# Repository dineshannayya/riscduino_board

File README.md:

# riscduino_board
Riscduino PCB Board documentation

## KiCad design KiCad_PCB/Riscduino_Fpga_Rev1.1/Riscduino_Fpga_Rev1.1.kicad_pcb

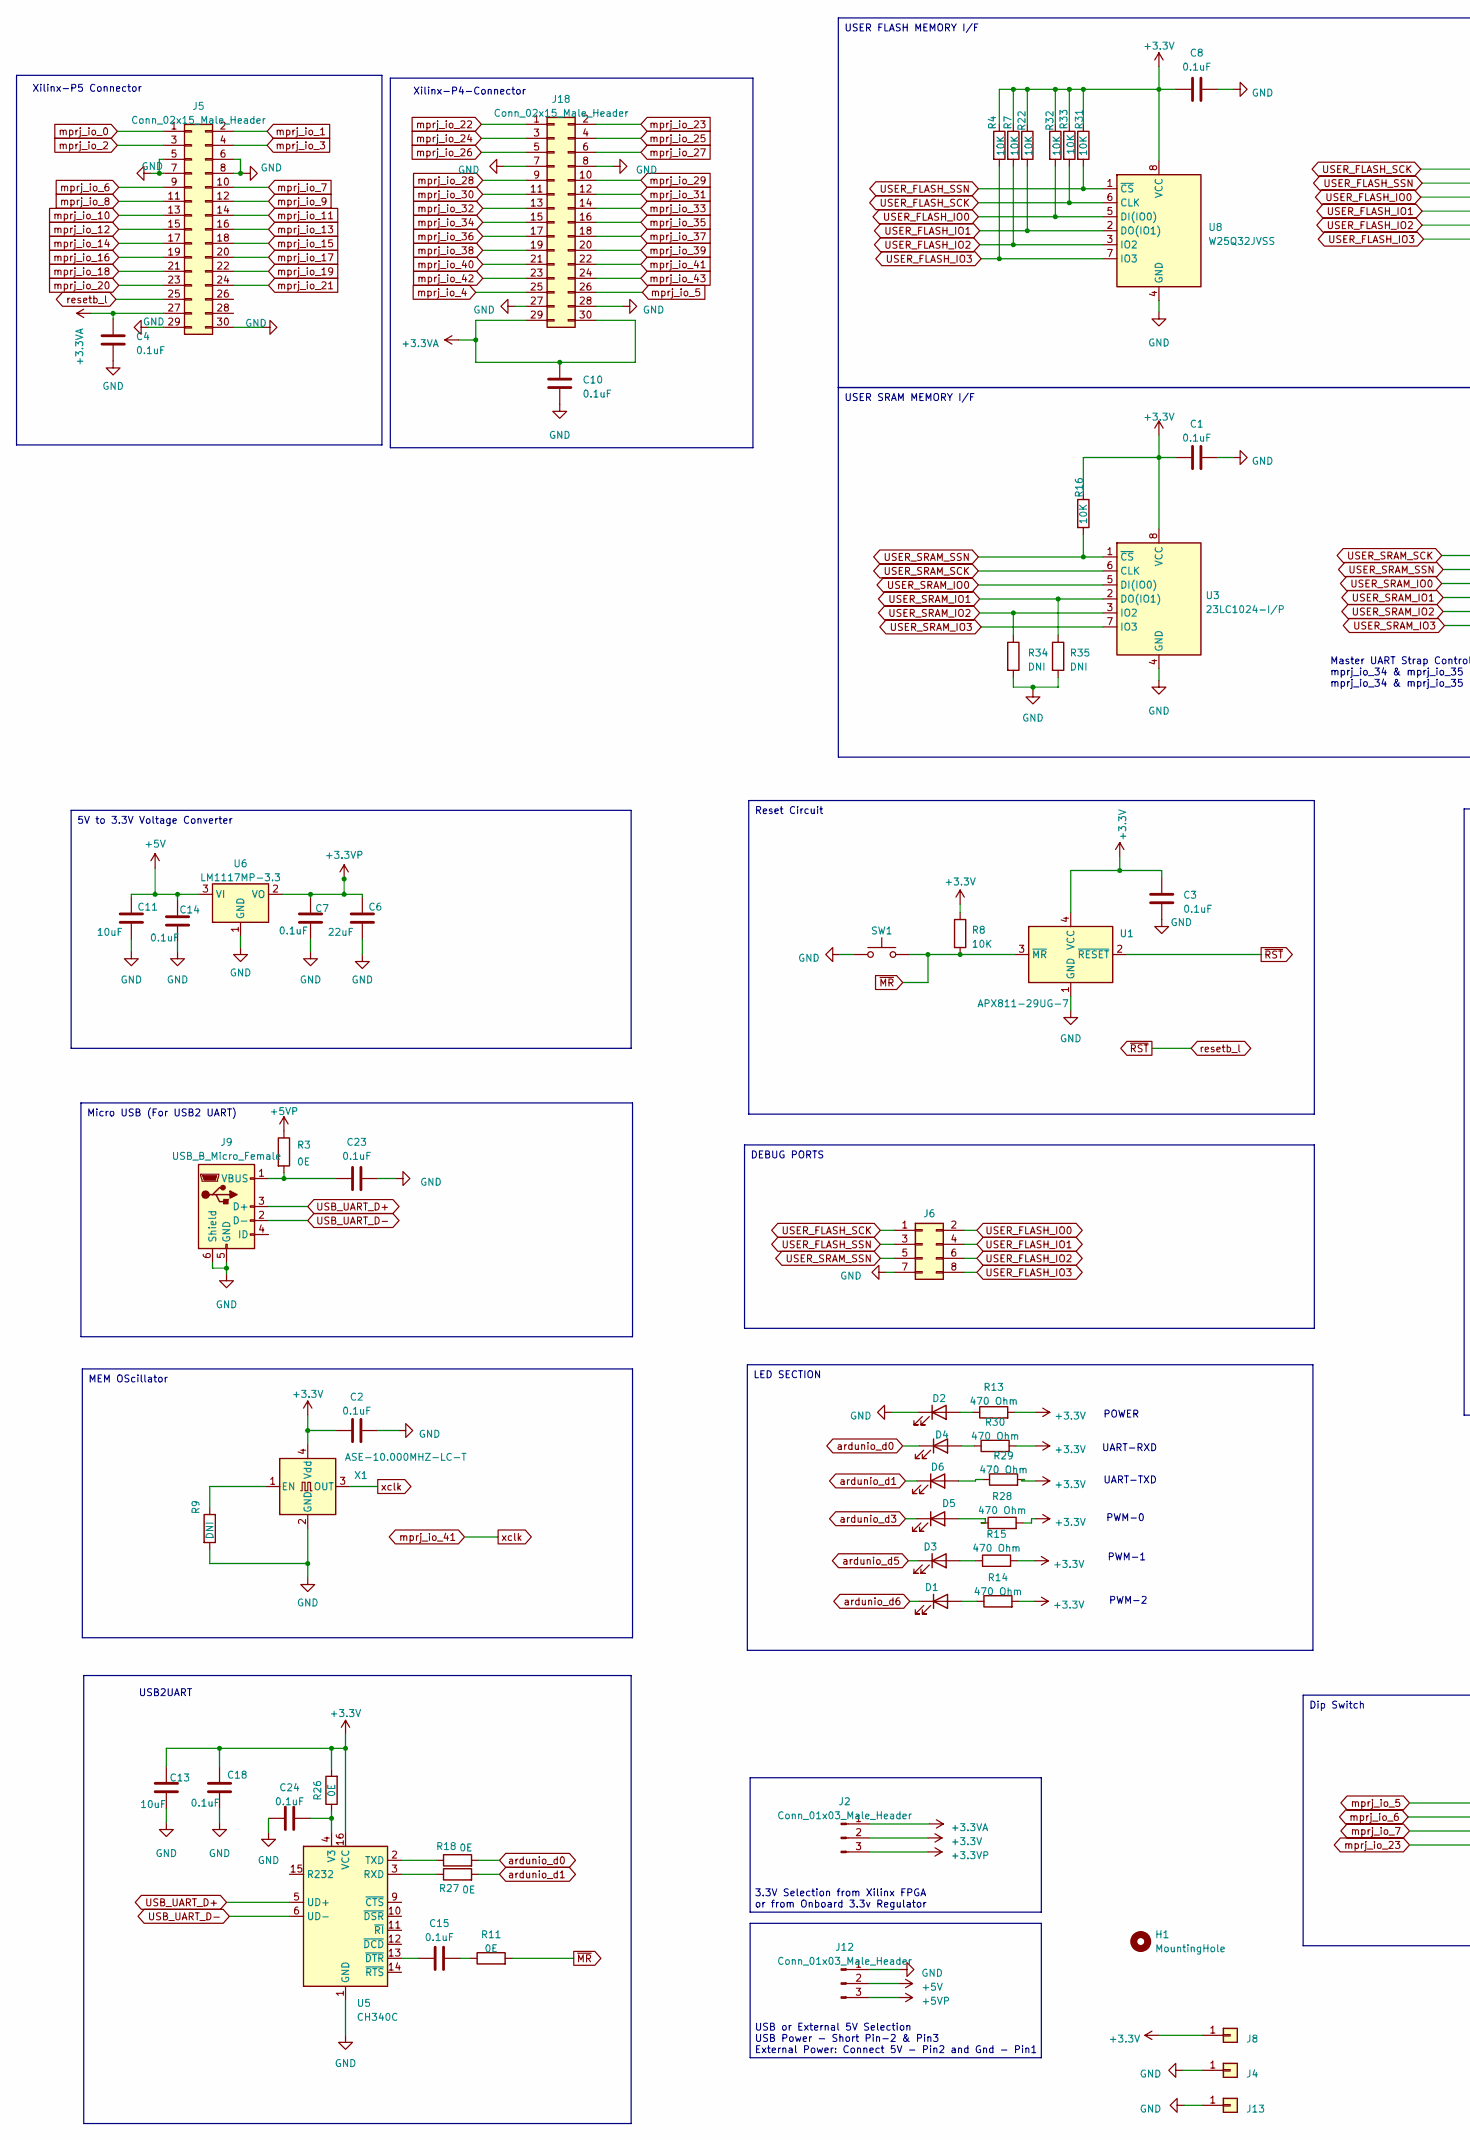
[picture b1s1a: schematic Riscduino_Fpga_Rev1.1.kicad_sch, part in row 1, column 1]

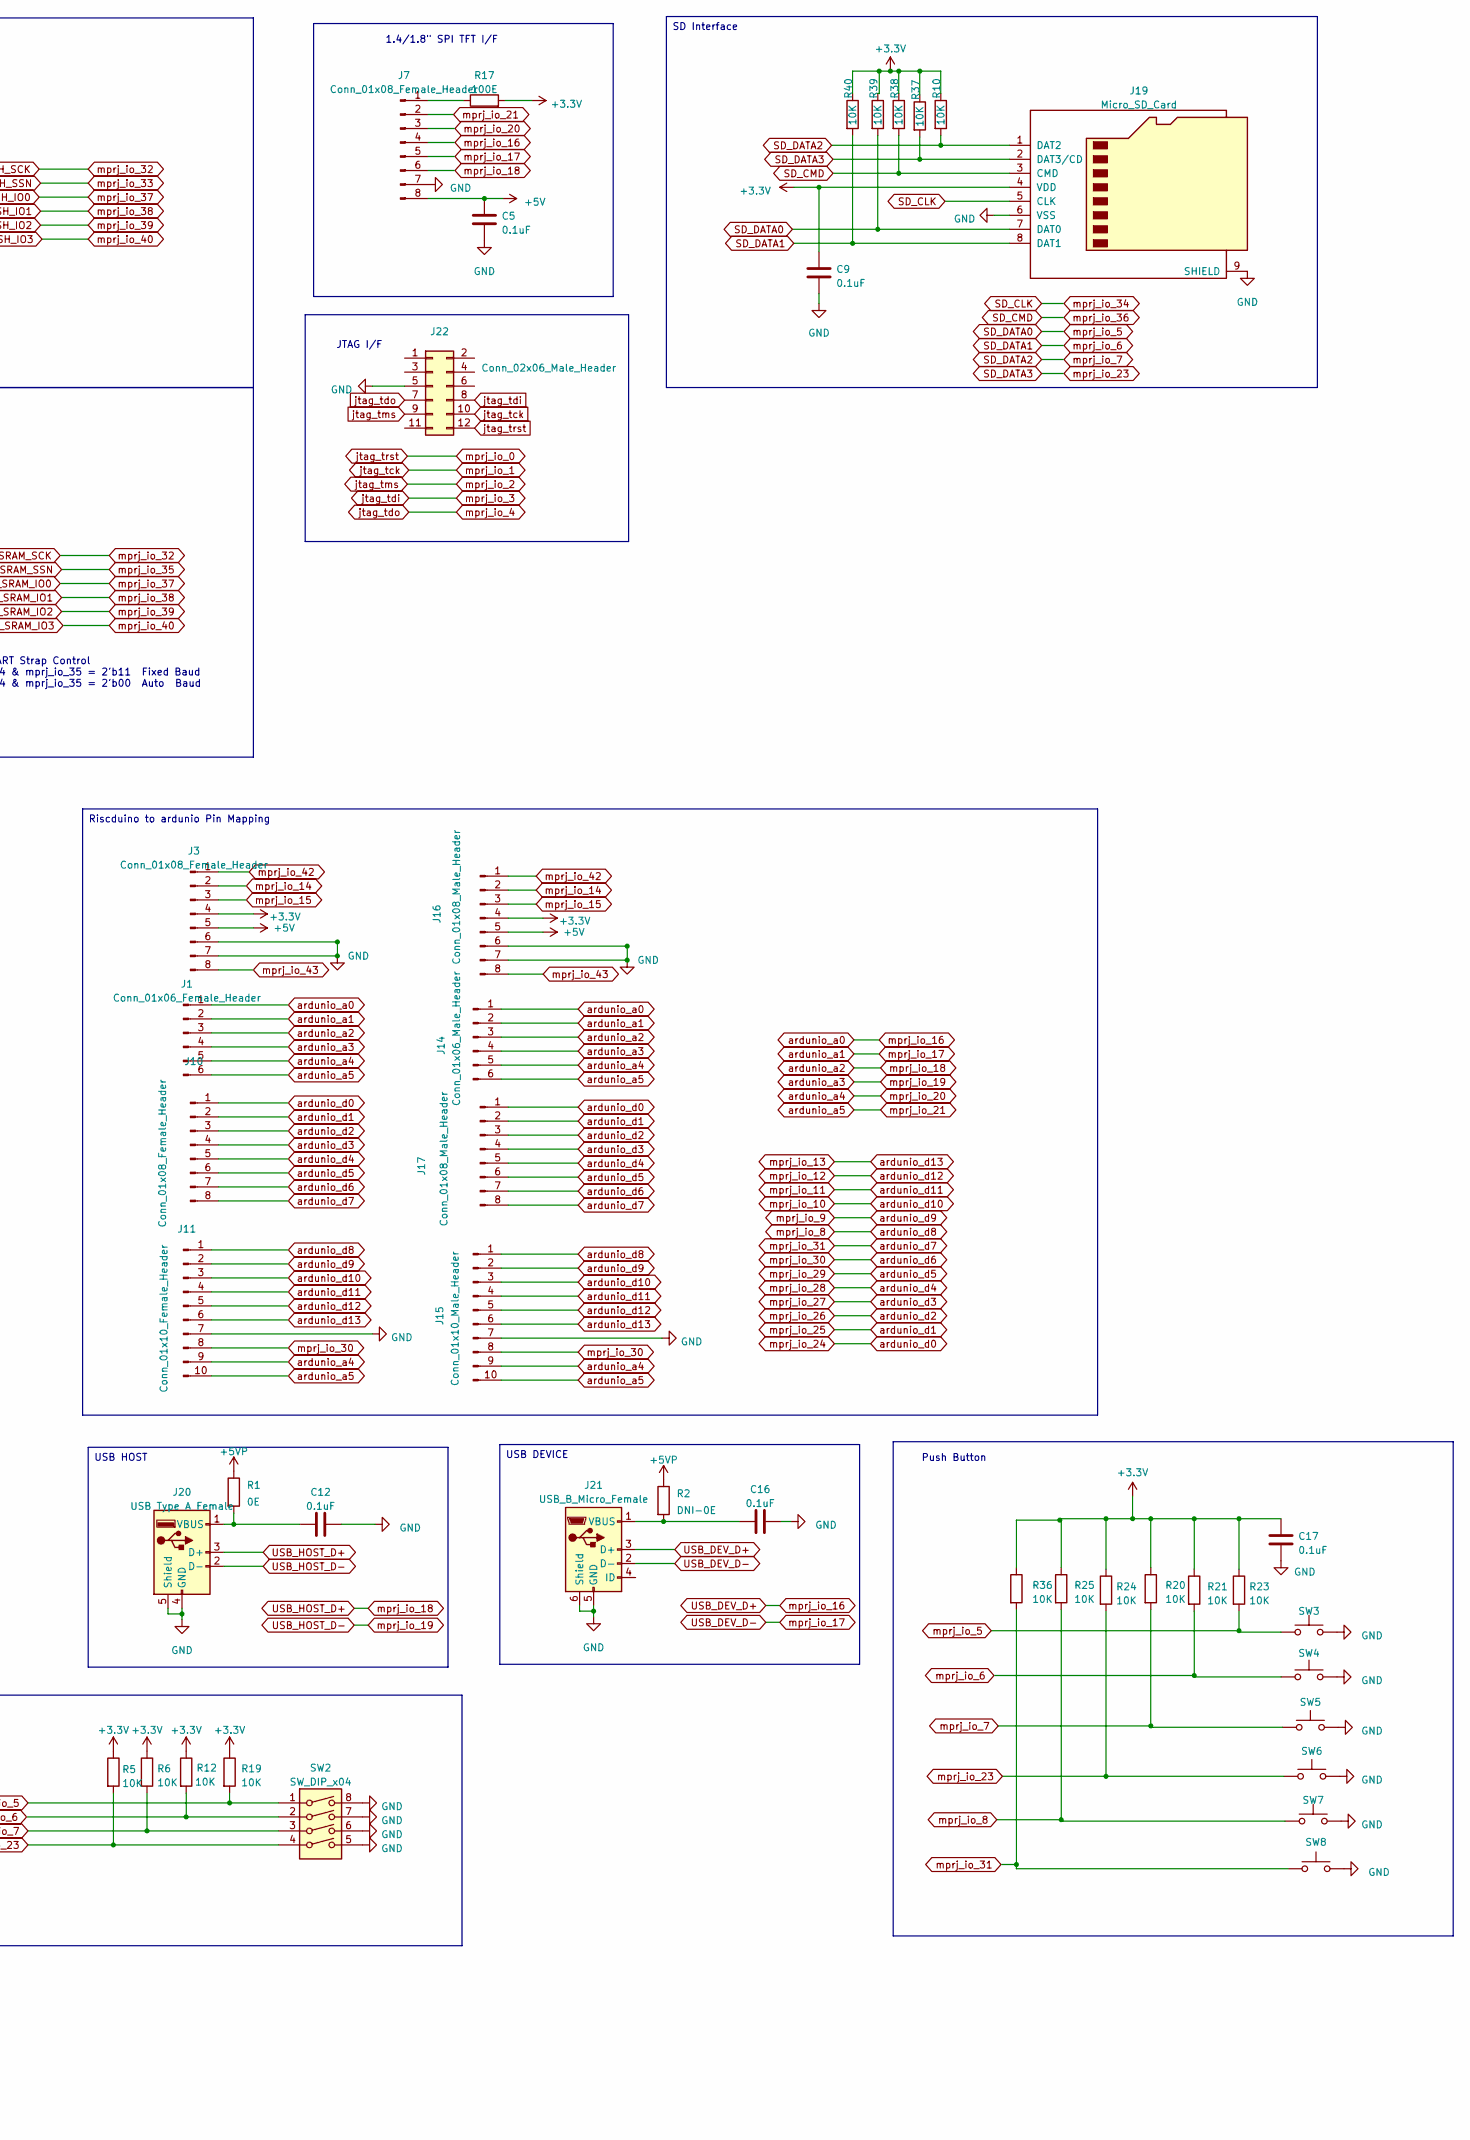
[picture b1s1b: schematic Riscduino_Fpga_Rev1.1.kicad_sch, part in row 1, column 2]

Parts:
C1, C2, C3, C4, C5, C7, C8, C9, C10, C12, C14, C15, C16, C17, C18, C23, C24: 0.1uF; C_0603_1608Metric_Pad1.08x0.95mm_HandSolder
C6: 22uF; C_0805_2012Metric_Pad1.18x1.45mm_HandSolder
C11, C13: 10uF; C_0805_2012Metric_Pad1.18x1.45mm_HandSolder
D1, D3, D5, D6: BLUE LED; LED_0805_2012Metric_Pad1.15x1.40mm_HandSolder
D2, D4: GREEN LED; LED_0805_2012Metric_Pad1.15x1.40mm_HandSolder
H1: MountingHole; Arduino_UNO_R3_WithMountingHoles
J1: Conn_01x06_Female_Header; PinHeader_1x06_P2.54mm_Vertical
J2, J12: Conn_01x03_Male_Header; PinHeader_1x03_P2.54mm_Vertical
J3, J7, J10: Conn_01x08_Female_Header; PinHeader_1x08_P2.54mm_Vertical
J4, J8, J13: Conn_01x01; PinHeader_1x01_P2.54mm_Vertical
J5, J18: Conn_02x15_Male_Header; PinHeader_2x15_P2.54mm_Vertical
J6: Conn_02x04_Male_Header; PinHeader_2x04_P2.54mm_Vertical
J9, J21: USB_B_Micro_Female; USB_Micro-B_Molex-105017-0001
J11: Conn_01x10_Female_Header; PinHeader_1x10_P2.54mm_Vertical
J14: Conn_01x06_Male_Header; PinHeader_1x06_P2.54mm_Vertical
J15: Conn_01x10_Male_Header; PinHeader_1x10_P2.54mm_Vertical
J16, J17: Conn_01x08_Male_Header; PinHeader_1x08_P2.54mm_Vertical
J19: Micro_SD_Card; microSD_HC_Molex_104031-0811
J20: USB Type A Female; USB_A_Molex_67643_Horizontal
J22: Conn_02x06_Male_Header; PinHeader_2x06_P2.54mm_Vertical
R1, R3, R11, R18, R26, R27: 0E; R_0603_1608Metric_Pad0.98x0.95mm_HandSolder
R2: DNI-0E; R_0603_1608Metric_Pad0.98x0.95mm_HandSolder
R4, R5, R6, R7, R8, R10, R12, R16, R19, R20, R21, R22, R23, R24, R25, R31, R32, R33, R36, R37, R38, R39, R40: 10K; R_0603_1608Metric_Pad0.98x0.95mm_HandSolder
R9, R34, R35: DNI; R_0603_1608Metric_Pad0.98x0.95mm_HandSolder
R13, R14, R15, R28, R29, R30: 470 Ohm; R_0603_1608Metric_Pad0.98x0.95mm_HandSolder
R17: 100E; R_0603_1608Metric_Pad0.98x0.95mm_HandSolder
SW1, SW3, SW4, SW5, SW6, SW7, SW8: 4Pin Round Button SPST Straight Tactile Switch SM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; SW_SPST_EVPBF_TS4550TP
SW2: SW_DIP_x04; DIP-8_W7.62mm_LongPads
U1: APX811-29UG-7; SOT-143_Handsoldering
U3: 23LC1024-I/P; DIP-8_W7.62mm_LongPads
U5: CH340C; SOIC-16_3.9x9.9mm_P1.27mm
U6: LM1117MP-3.3; SOT-223-3_TabPin2
U8: W25Q32JVSS; SOIC-8_5.23x5.23mm_P1.27mm
X1: ASE-10.000MHZ-LC-T; Crystal_SMD_Abracon_ABM8G-4Pin_3.2x2.5mm

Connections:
+3.3V: C1.1, C2.1, C3.1, C8.1, C9.1, C13.1, C17.1, C18.1, J2.2, J3.4, J8.1, J16.4, J19.4 (VDD), R4.1, R5.1, R6.1, R7.1, R8.1, R10.1, R12.1, R13.2, R14.2, R15.2, R16.1, R17.2, R19.1, R20.1, R21.1, R22.1, R23.1, R24.1, R25.1, R26.2, R28.2, R29.2, R30.2, R31.1, R32.1, R33.1, R36.1, R37.1, R38.1, R39.1, R40.1, U1.4 (VCC), U3.8 (VCC), U5.16 (VCC), U8.8 (VCC), X1.4 (Vdd)
+3.3VA: C4.1, C10.1, J2.1, J5.27, J18.29, J18.30
+3.3VP: C6.1, C7.1, J2.3, U6.2 (VO)
+5V: C5.1, C11.1, C14.1, J3.5, J7.8, J12.2, J16.5, U6.3 (VI)
+5VP: J12.3, R1.1, R2.1, R3.1
GND: C1.2, C2.2, C3.2, C4.2, C5.2, C6.2, C7.2, C8.2, C9.2, C10.2, C11.2, C12.2, C13.2, C14.2, C16.2, C17.2, C18.2, C23.2, C24.1, D2.1 (K), J3.6, J3.7, J4.1, J5.5, J5.6, J5.7, J5.8, J5.29, J5.30, J6.7, J7.7, J9.5 (GND), J9.6 (Shield), J11.7, J12.1, J13.1, J15.7, J16.6, J16.7, J18.7, J18.8, J18.27, J18.28, J19.6 (VSS), J19.9 (SHIELD), J20.4 (GND), J20.5 (Shield), J21.5 (GND), J21.6 (Shield), J22.5, R9.2, R34.2, R35.2, SW1.1, SW2.5, SW2.6, SW2.7, SW2.8, SW3.2, SW4.2, SW5.2, SW6.2, SW7.2, SW8.2, U1.1 (GND), U3.4 (GND), U5.1 (GND), U6.1 (GND), U8.4 (GND), X1.2 (GND)
unnamed: C15.2, R11.1
unnamed 7: D1.2 (A), R14.1; also elsewhere on the board
unnamed: D2.2 (A), R13.1
unnamed: D3.2 (A), R15.1
unnamed: D4.2 (A), R30.1
unnamed: D5.2 (A), R28.1
unnamed: D6.2 (A), R29.1
unnamed: J7.1, R17.1
unnamed: C23.1, J9.1 (VBUS), R3.2
unnamed: C12.1, J20.1 (VBUS), R1.2
unnamed: C16.1, J21.1 (VBUS), R2.2
unnamed: R27.1, U5.3 (RXD)
unnamed: R18.1, U5.2 (TXD)
unnamed: C24.2, R26.1, U5.4 (V3)
unnamed: C15.1, U5.13 (~DTR)
unnamed: R9.1, X1.1 (EN)
SD_CLK: J18.15, J19.5 (CLK)
SD_CMD: J18.17, J19.3 (CMD), R38.2
SD_DATA0: J18.26, J19.7 (DAT0), R19.2, R23.2, R39.2, SW2.1, SW3.1
SD_DATA1: J5.9, J19.8 (DAT1), R12.2, R21.2, R40.2, SW2.2, SW4.1
SD_DATA2: J5.10, J19.1 (DAT2), R6.2, R10.2, R20.2, SW2.3, SW5.1
SD_DATA3: J18.2, J19.2 (DAT3/CD), R5.2, R24.2, R37.2, SW2.4, SW6.1
USB_DEV_D+: J1.1, J5.19, J7.4, J14.1, J21.3 (D+)
USB_DEV_D-: J1.2, J5.20, J7.5, J14.2, J21.2 (D-)
USB_HOST_D+: J1.3, J5.21, J7.6, J14.3, J20.3 (D+)
USB_HOST_D-: J1.4, J5.22, J14.4, J20.2 (D-)
USB_UART_D+: J9.3 (D+), U5.5 (UD+)
USB_UART_D-: J9.2 (D-), U5.6 (UD-)
USER_FLASH_IO0: J6.2, J18.18, R32.2, U3.5 (DI(IO0)), U8.5 (DI(IO0))
USER_FLASH_IO1: J6.4, J18.19, R22.2, R35.1, U3.2 (DO(IO1)), U8.2 (DO(IO1))
USER_FLASH_IO2: J6.6, J18.20, R7.2, R34.1, U3.3 (IO2), U8.3 (IO2)
USER_FLASH_IO3: J6.8, J18.21, R4.2, U3.7 (IO3), U8.7 (IO3)
USER_FLASH_SCK: J6.1, J18.13, R33.2, U3.6 (CLK), U8.6 (CLK)
USER_FLASH_SSN: J6.3, J18.14, R31.2, U8.1 (~CS)
USER_SRAM_SSN: J6.5, J18.16, R16.2, U3.1 (~CS)
ardunio_a4: J1.5, J5.23, J7.3, J11.9, J14.5, J15.9
ardunio_a5: J1.6, J5.24, J7.2, J11.10, J14.6, J15.10
ardunio_d0: D4.1 (K), J10.1, J17.1, J18.3, R18.2
ardunio_d1: D6.1 (K), J10.2, J17.2, J18.4, R27.2
ardunio_d2: J10.3, J17.3, J18.5
ardunio_d3: D5.1 (K), J10.4, J17.4, J18.6
ardunio_d4: J10.5, J17.5, J18.9
ardunio_d5: D3.1 (K), J10.6, J17.6, J18.10
ardunio_d6: D1.1 (K), J10.7, J11.8, J15.8, J17.7, J18.11; also elsewhere on the board
ardunio_d7: J10.8, J17.8, J18.12, R36.2, SW8.1
ardunio_d8: J5.11, J11.1, J15.1, R25.2, SW7.1
ardunio_d9: J5.12, J11.2, J15.2
ardunio_d10: J5.13, J11.3, J15.3
ardunio_d11: J5.14, J11.4, J15.4
ardunio_d12: J5.15, J11.5, J15.5
ardunio_d13: J5.16, J11.6, J15.6
jtag_tck: J5.2, J22.10
jtag_tdi: J5.4, J22.8
jtag_tdo: J18.25, J22.7
jtag_tms: J5.3, J22.9
jtag_trst: J5.1, J22.12
mprj_io_14: J3.2, J5.17, J16.2
mprj_io_15: J3.3, J5.18, J16.3
mprj_io_22: J18.1
mprj_io_41: J18.22, X1.3 (OUT)
mprj_io_42: J3.1, J16.1, J18.23
mprj_io_43: J3.8, J16.8, J18.24
resetb_l: J5.25, U1.2 (~RESET)
~MR: R8.2, R11.2, SW1.2, U1.3 (~MR)

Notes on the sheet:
MEM OScillator
5V to 3.3V Voltage Converter
Dip Switch
LED SECTION
Riscduino to ardunio Pin Mapping
Micro USB (For USB2 UART)
USER SRAM MEMORY I/F
DEBUG PORTS
USB HOST
USB DEVICE
USER FLASH MEMORY I/F
SD Interface
Reset Circuit
Xilinx-P5 Connector
POWER
Xilinx-P4-Connector
Push Button
UART-TXD
3.3V Selection from Xilinx FPGA or from Onboard 3.3v Regulator
JTAG I/F
USB or External 5V Selection USB Power - Short Pin-2 & Pin3 External Power: Connect 5V - Pin2 and Gnd - Pin1
PWM-0
UART-RXD
1.4/1.8" SPI TFT I/F
Master UART Strap Control mprj_io_34 & mprj_io_35 = 2'b11 Fixed Baud mprj_io_34 & mprj_io_35 = 2'b00 Auto Baud
PWM-1
USB2UART
PWM-2

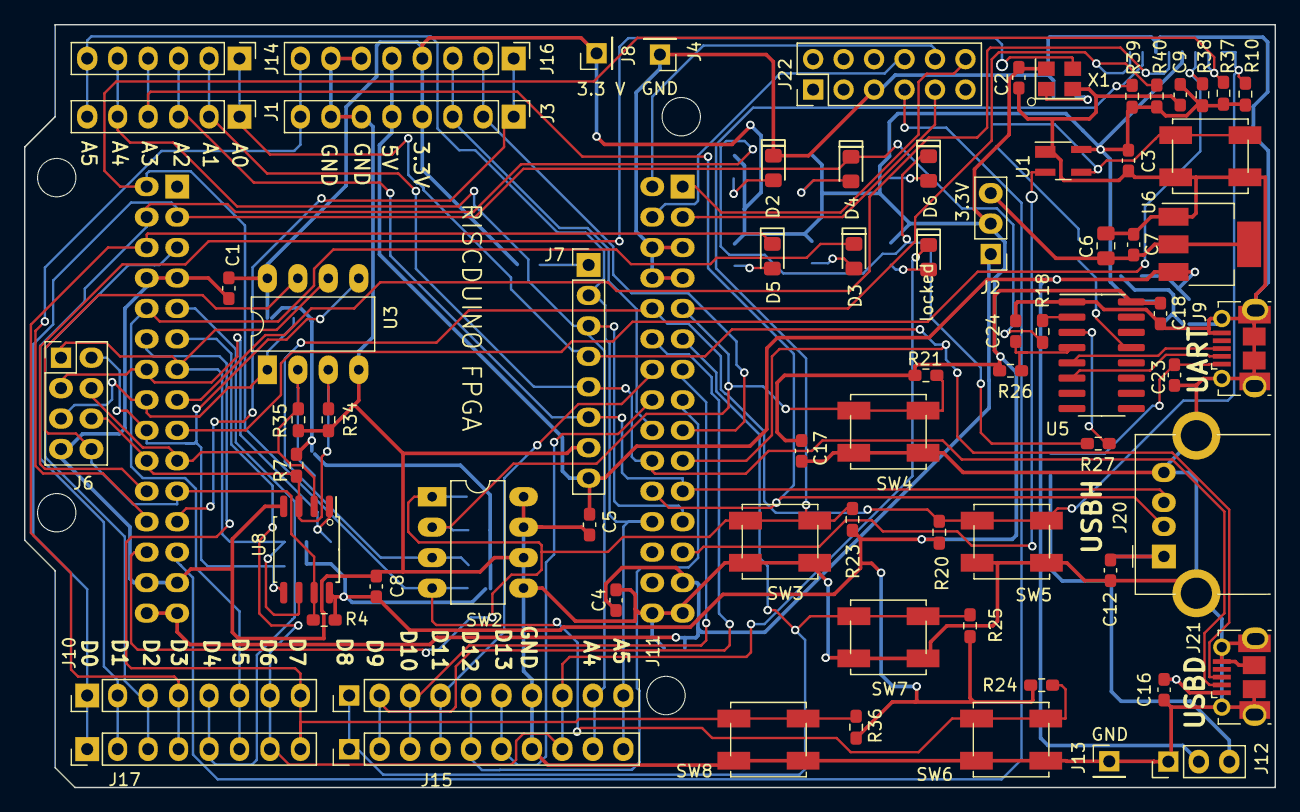
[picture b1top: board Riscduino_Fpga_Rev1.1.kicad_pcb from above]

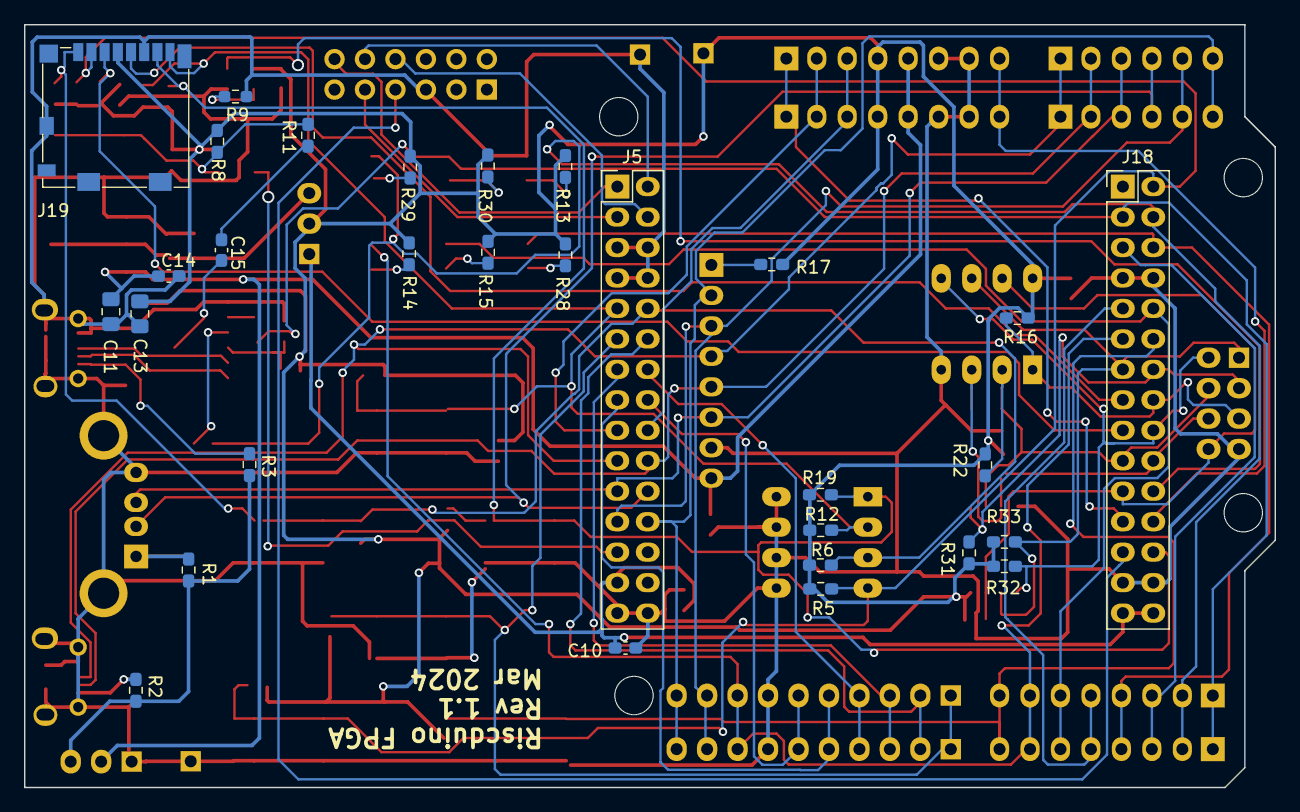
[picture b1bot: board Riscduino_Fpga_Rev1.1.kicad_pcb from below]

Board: 2 copper layers, 104.3 x 63.6 mm, 103 parts (30 on the bottom side), 69 nets.

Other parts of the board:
locked: BLUE LED; LED_0805_2012Metric_Pad1.15x1.40mm_HandSolder

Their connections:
unnamed 7: locked.2 (A); also elsewhere on the board
ardunio_d6: locked.1 (K); also elsewhere on the board

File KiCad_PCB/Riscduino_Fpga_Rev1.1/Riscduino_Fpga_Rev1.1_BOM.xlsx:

Id | Designator | Footprint | Quantity | Designation | Supplier and ref | Column1 | _1
1 | J4,J13,J8 | PinHeader_1x01_P2.54mm_Vertical | 3 | Conn_01x01
5 | J3,J10,J7 | PinHeader_1x08_P2.54mm_Vertical | 3 | Conn_01x08_Female_Header
11 | J1 | PinHeader_1x06_P2.54mm_Vertical | 1 | Conn_01x06_Female_Header
25 | J11 | PinHeader_1x10_P2.54mm_Vertical | 1 | Conn_01x10_Female_Header
7 | J6 | PinHeader_2x04_P2.54mm_Vertical | 1 | Conn_02x04_Male_Header
15 | J14 | PinHeader_1x06_P2.54mm_Vertical | 1 | Conn_01x06_Male_Header
17 | J16,J17 | PinHeader_1x08_P2.54mm_Vertical | 2 | Conn_01x08_Male_Header
23 | J15 | PinHeader_1x10_P2.54mm_Vertical | 1 | Conn_01x10_Male_Header
28 | J12,J2 | PinHeader_1x03_P2.54mm_Vertical | 2 | Conn_01x03_Male_Header
30 | J22 | PinHeader_2x06_P2.54mm_Vertical | 1 | Conn_02x06_Male_Header
34 | J5,J18 | PinHeader_2x15_P2.54mm_Vertical | 2 | Conn_02x15_Male_Header (Double Hight, Both side exposure)
21 | J9,J21 | USB_Micro-B_Molex-105017-0001 | 2 | USB_B_Micro_Female
19 | J20 | USB_A_Molex_67643_Horizontal | 1 | USB Type A Female
8 | C1,C2,C3,C4,C5,C7,C8,C9,C10,C12,C14,C15,C16,C17,C18,C23,C24 | C_0603_1608Metric_Pad1.08x0.95mm_HandSolder | 17 | 0.1uF
10 | C6 | C_0805_2012Metric_Pad1.18x1.45mm_HandSolder | 1 | 22uF
33 | C13,C11 | C_0805_2012Metric_Pad1.18x1.45mm_HandSolder | 2 | 10uF
4 | R38,R25,R23,R39,R21,R37,R20,R24,R4,R10,R36,R7,R40,R5,R8,R19,R22,R31,R6,R32,R33,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 | R_0603_1608Metric_Pad0.98x0.95mm_HandSolder | 23 | 10K
16 | R1,R3,R11,R18,R26,R27 | R_0603_1608Metric_Pad0.98x0.95mm_HandSolder | 6 | 0E
31 | R13,R29,R28,R14,R15,R30 | R_0603_1608Metric_Pad0.98x0.95mm_HandSolder | 6 | 470 Ohm
32 | R17 | R_0603_1608Metric_Pad0.98x0.95mm_HandSolder | 1 | 100E
2 | U6 | SOT-223-3_TabPin2 | 1 | LM1117MP-3.3
3 | U8 | SOIC-8_5.23x5.23mm_P1.27mm | 1 | W25Q32JVSS
6 | U5 | SOIC-16_3.9x9.9mm_P1.27mm | 1 | CH340C
12 | D2,D4 | LED_0805_2012Metric_Pad1.15x1.40mm_HandSolder | 2 | GREEN LED
14 | D3,D1,D5,D6 | LED_0805_2012Metric_Pad1.15x1.40mm_HandSolder | 4 | BLUE LED
13 | SW3,SW5,SW8,SW6,SW4,SW1,SW7 | SW_SPST_EVPBF_TS4550TP | 7 | 4Pin Round Button SPST Straight Tactile Switch SMD - TS4550TP
18 | SW2 | DIP-8_W7.62mm_LongPads | 1 | 8 bit DIP Socket (SW_DIP_x04)
26 | U3 | DIP-8_W7.62mm_LongPads | 1 | 8 pin DIP socket (23LC1024-I/P)
27 | U1 | SOT-143_Handsoldering | 1 | APX811-29UG-7
29 | X1 | Crystal_SMD_Abracon_ABM8G-4Pin_3.2x2.5mm | 1 | ASE-10.000MHZ-LC-T
DNI - Donot Mount
1 | R34,R35 | R_0603_1608Metric_Pad0.98x0.95mm_HandSolder | 2 | DNI
2 | R9 | R_0603_1608Metric_Pad0.98x0.95mm_HandSolder | 1 | DNI
3 | R2 | R_0603_1608Metric_Pad0.98x0.95mm_HandSolder | 1 | DNI-0E
4 | J19 | microSD_HC_Molex_104031-0811 | 1 | Micro_SD_Card
24 | H1 | Arduino_UNO_R3_WithMountingHoles | 1 | MountingHole
